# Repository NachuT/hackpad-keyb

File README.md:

# NT KEYB!!!
## Details
  1. Ortholinear custom layout
  2. Minimalist
  3. Cross Wirred PCB
  4. Uses a Pi Pico (or maybe an Orpheus pico 😀)
  5. One piece case but added holes just in case I feel like changing my mind in the future

## BOM
  1. PCB
  2. Case (1 part)
  3. 67 Standard Mx switches
  4. 63 standard 1u keycaps
  5. 1 6u keycap + 6u stabilizer
  6. 3 2u keycaps + 2u stabilizer

## Pictures!

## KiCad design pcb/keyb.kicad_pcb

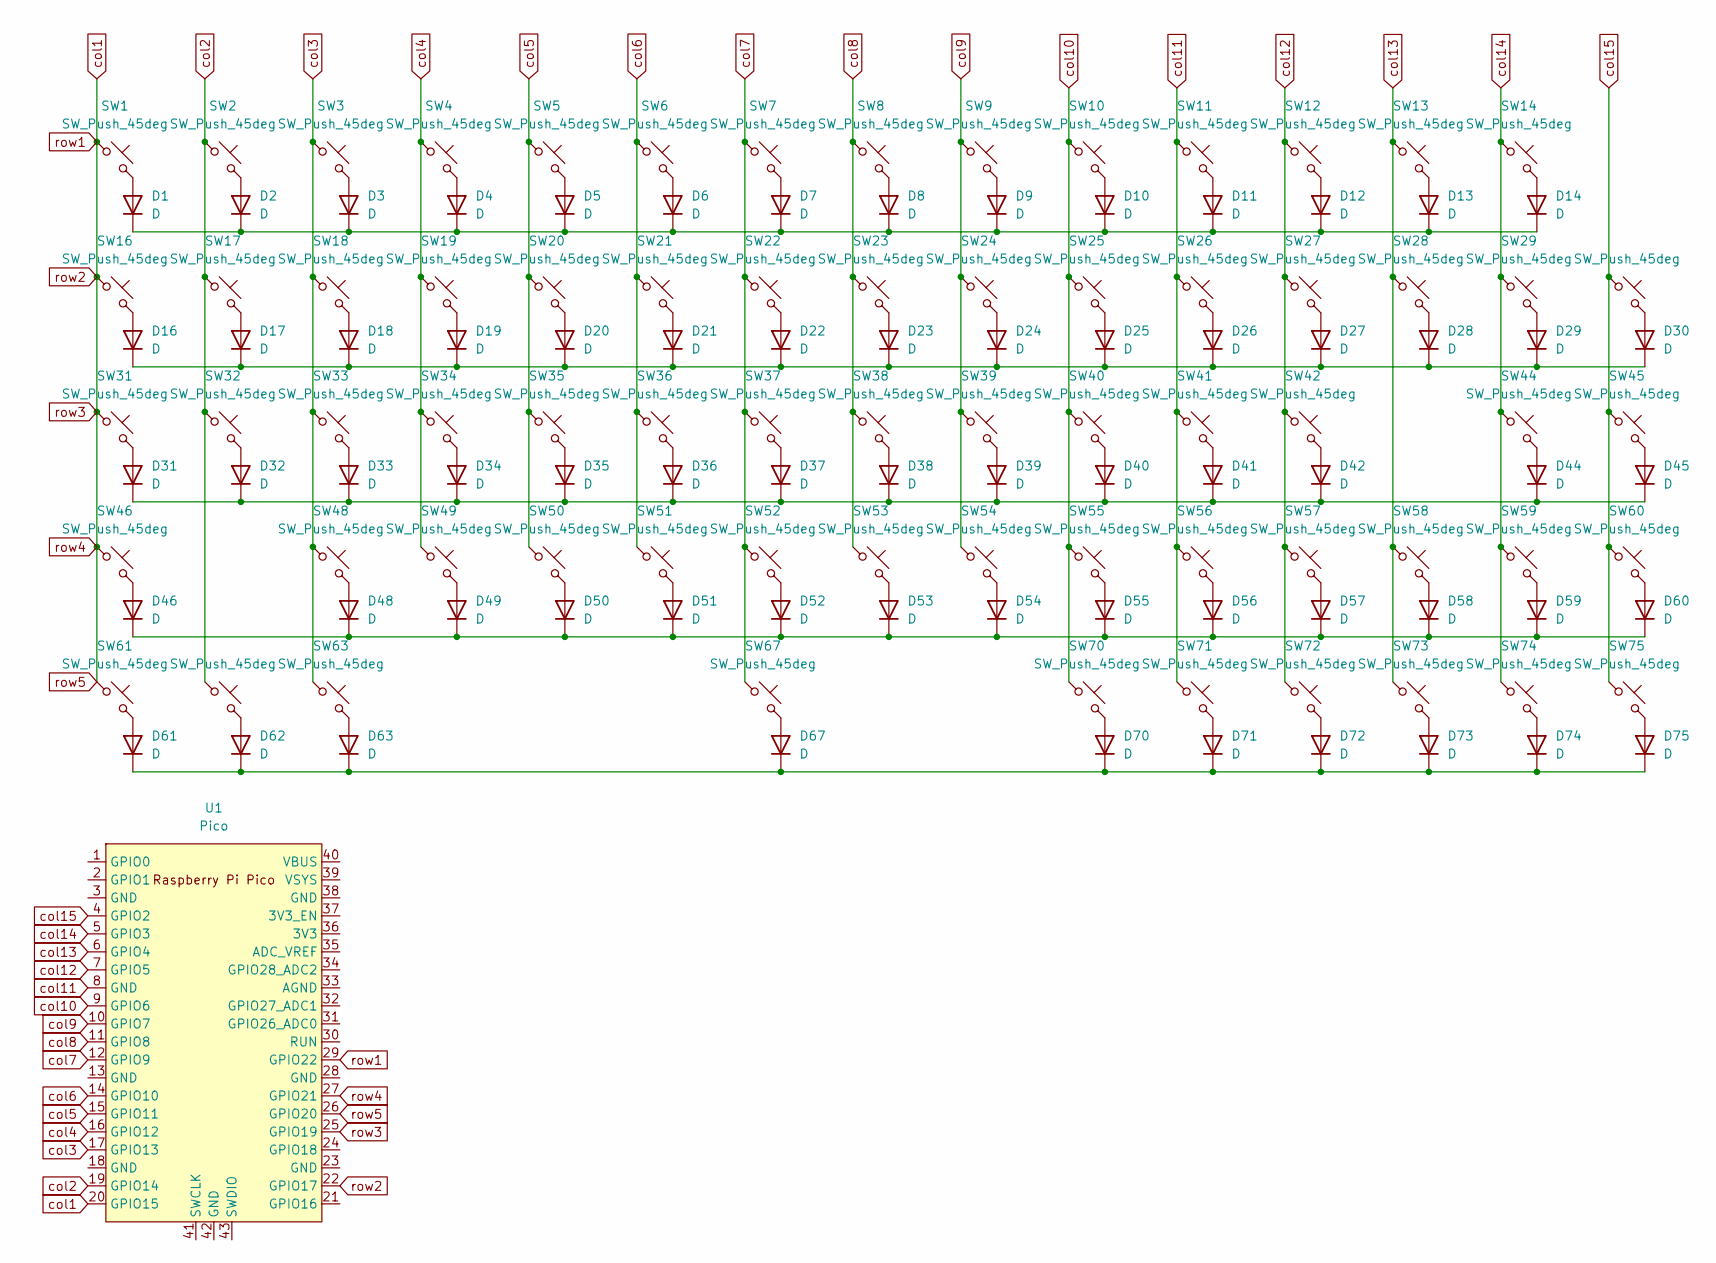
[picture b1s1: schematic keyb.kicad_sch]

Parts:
D1, D2, D3, D4, D5, D6, D7, D8, D9, D10, D11, D12, D13, D14, D16, D17, D18, D19, D20, D21, D22, D23, D24, D25, D26, D27, D28, D29, D30, D31, D32, D33, D34, D35, D36, D37, D38, D39, D40, D41, D42, D44, D45, D46, D48, D49, D50, D51, D52, D53, D54, D55, D56, D57, D58, D59, D60, D61, D62, D63, D67, D70, D71, D72, D73, D74, D75: D; Diode_DO-35
SW1, SW2, SW3, SW4, SW5, SW6, SW7, SW8, SW9, SW10, SW11, SW12, SW13, SW16, SW17, SW18, SW19, SW20, SW21, SW22, SW23, SW24, SW25, SW26, SW27, SW28, SW29, SW30, SW31, SW32, SW33, SW34, SW35, SW36, SW37, SW38, SW39, SW40, SW41, SW42, SW45, SW48, SW49, SW50, SW51, SW52, SW53, SW54, SW55, SW56, SW57, SW58, SW59, SW60, SW61, SW62, SW63, SW70, SW71, SW72, SW73, SW74, SW75: SW_Push_45deg; SW_Cherry_MX_1.00u_PCB
SW14, SW44, SW46: SW_Push_45deg; SW_Cherry_MX_2.00u_PCB
SW67: SW_Push_45deg; MX-6U
U1: Pico; RaspberryPi_Pico_Common_THT

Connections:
unnamed: D1.2 (A), SW1.2
unnamed: D1.1 (K), D2.1 (K), D3.1 (K), D4.1 (K), D5.1 (K), D6.1 (K), D7.1 (K), D8.1 (K), D9.1 (K), D10.1 (K), D11.1 (K), D12.1 (K), D13.1 (K), D14.1 (K)
unnamed: D2.2 (A), SW2.2
unnamed: D3.2 (A), SW3.2
unnamed: D4.2 (A), SW4.2
unnamed: D5.2 (A), SW5.2
unnamed: D6.2 (A), SW6.2
unnamed: D7.2 (A), SW7.2
unnamed: D8.2 (A), SW8.2
unnamed: D9.2 (A), SW9.2
unnamed: D10.2 (A), SW10.2
unnamed: D11.2 (A), SW11.2
unnamed: D12.2 (A), SW12.2
unnamed: D13.2 (A), SW13.2
unnamed: D14.2 (A), SW14.2
unnamed: D16.2 (A), SW16.2
unnamed: D16.1 (K), D17.1 (K), D18.1 (K), D19.1 (K), D20.1 (K), D21.1 (K), D22.1 (K), D23.1 (K), D24.1 (K), D25.1 (K), D26.1 (K), D27.1 (K), D28.1 (K), D29.1 (K), D30.1 (K)
unnamed: D17.2 (A), SW17.2
unnamed: D18.2 (A), SW18.2
unnamed: D19.2 (A), SW19.2
unnamed: D20.2 (A), SW20.2
unnamed: D21.2 (A), SW21.2
unnamed: D22.2 (A), SW22.2
unnamed: D23.2 (A), SW23.2
unnamed: D24.2 (A), SW24.2
unnamed: D25.2 (A), SW25.2
unnamed: D26.2 (A), SW26.2
unnamed: D27.2 (A), SW27.2
unnamed: D28.2 (A), SW28.2
unnamed: D29.2 (A), SW29.2
unnamed: D30.2 (A), SW30.2
unnamed: D31.2 (A), SW31.2
unnamed: D31.1 (K), D32.1 (K), D33.1 (K), D34.1 (K), D35.1 (K), D36.1 (K), D37.1 (K), D38.1 (K), D39.1 (K), D40.1 (K), D41.1 (K), D42.1 (K), D44.1 (K), D45.1 (K)
unnamed: D32.2 (A), SW32.2
unnamed: D33.2 (A), SW33.2
unnamed: D34.2 (A), SW34.2
unnamed: D35.2 (A), SW35.2
unnamed: D36.2 (A), SW36.2
unnamed: D37.2 (A), SW37.2
unnamed: D38.2 (A), SW38.2
unnamed: D39.2 (A), SW39.2
unnamed: D40.2 (A), SW40.2
unnamed: D41.2 (A), SW41.2
unnamed: D42.2 (A), SW42.2
unnamed: D44.2 (A), SW44.2
unnamed: D45.2 (A), SW45.2
unnamed: D46.2 (A), SW46.2
unnamed: D46.1 (K), D48.1 (K), D49.1 (K), D50.1 (K), D51.1 (K), D52.1 (K), D53.1 (K), D54.1 (K), D55.1 (K), D56.1 (K), D57.1 (K), D58.1 (K), D59.1 (K), D60.1 (K)
unnamed: D48.2 (A), SW48.2
unnamed: D49.2 (A), SW49.2
unnamed: D50.2 (A), SW50.2
unnamed: D51.2 (A), SW51.2
unnamed: D52.2 (A), SW52.2
unnamed: D53.2 (A), SW53.2
unnamed: D54.2 (A), SW54.2
unnamed: D55.2 (A), SW55.2
unnamed: D56.2 (A), SW56.2
unnamed: D57.2 (A), SW57.2
unnamed: D58.2 (A), SW58.2
unnamed: D59.2 (A), SW59.2
unnamed: D60.2 (A), SW60.2
unnamed: D61.2 (A), SW61.2
unnamed: D61.1 (K), D62.1 (K), D63.1 (K), D67.1 (K), D70.1 (K), D71.1 (K), D72.1 (K), D73.1 (K), D74.1 (K), D75.1 (K)
unnamed: D62.2 (A), SW62.2
unnamed: D63.2 (A), SW63.2
unnamed: D67.2 (A), SW67.2
unnamed: D70.2 (A), SW70.2
unnamed: D71.2 (A), SW71.2
unnamed: D72.2 (A), SW72.2
unnamed: D73.2 (A), SW73.2
unnamed: D74.2 (A), SW74.2
unnamed: D75.2 (A), SW75.2
col1: SW1.1, SW16.1, SW31.1, SW46.1, SW61.1, U1.20 (GPIO15), U1.22 (GPIO17), U1.25 (GPIO19), U1.26 (GPIO20), U1.27 (GPIO21), U1.29 (GPIO22)
col2: SW2.1, SW17.1, SW32.1, SW62.1, U1.19 (GPIO14)
col3: SW3.1, SW18.1, SW33.1, SW48.1, SW63.1, U1.17 (GPIO13)
col4: SW4.1, SW19.1, SW34.1, SW49.1, U1.16 (GPIO12)
col5: SW5.1, SW20.1, SW35.1, SW50.1, U1.15 (GPIO11)
col6: SW6.1, SW21.1, SW36.1, SW51.1, U1.14 (GPIO10)
col7: SW7.1, SW22.1, SW37.1, SW52.1, SW67.1, U1.12 (GPIO9)
col8: SW8.1, SW23.1, SW38.1, SW53.1, U1.11 (GPIO8)
col9: SW9.1, SW24.1, SW39.1, SW54.1, U1.10 (GPIO7)
col10: SW10.1, SW25.1, SW40.1, SW55.1, SW70.1, U1.9 (GPIO6)
col11: SW11.1, SW26.1, SW41.1, SW56.1, SW71.1, U1.8 (GND)
col12: SW12.1, SW27.1, SW42.1, SW57.1, SW72.1, U1.7 (GPIO5)
col13: SW13.1, SW28.1, SW58.1, SW73.1, U1.6 (GPIO4)
col14: SW14.1, SW29.1, SW44.1, SW59.1, SW74.1, U1.5 (GPIO3)
col15: SW30.1, SW45.1, SW60.1, SW75.1, U1.4 (GPIO2)

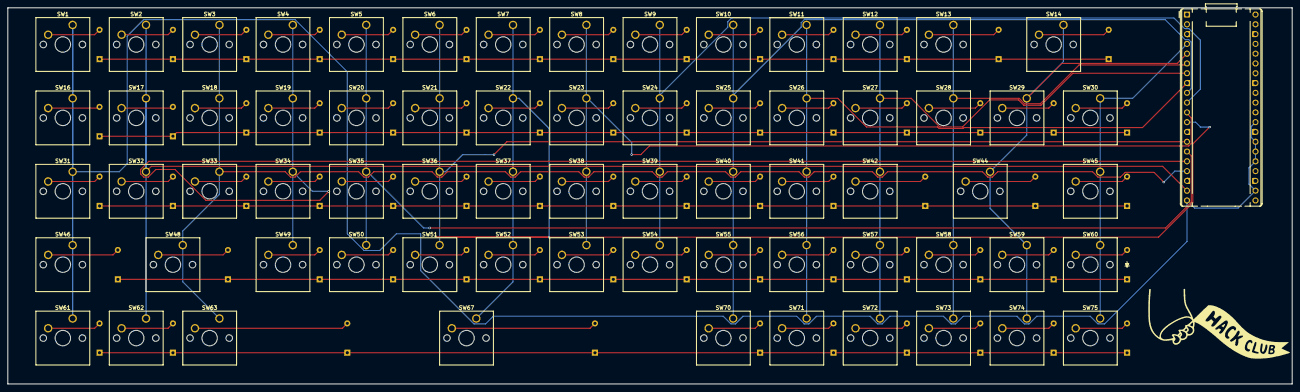
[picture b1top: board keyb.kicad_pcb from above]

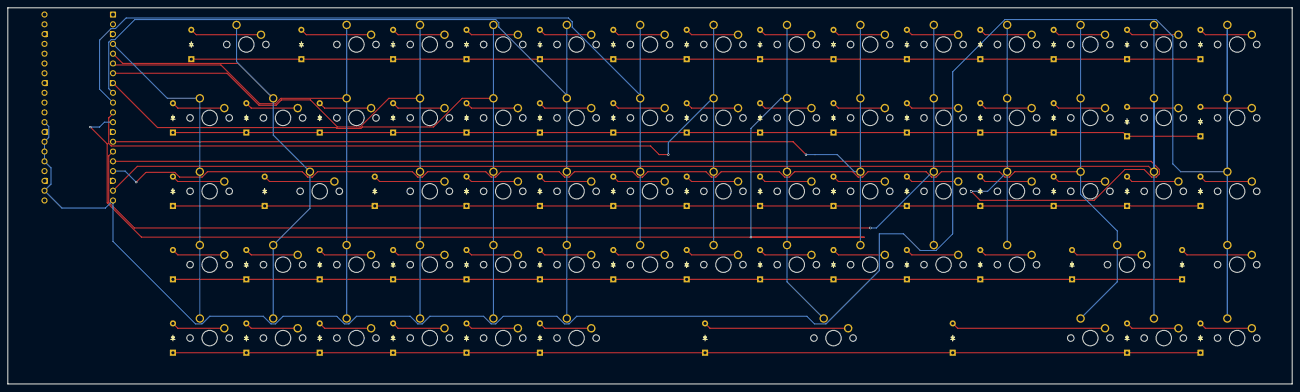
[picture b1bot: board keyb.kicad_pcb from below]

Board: 2 copper layers, 333.4 x 97.6 mm, 135 parts (66 on the bottom side), 87 nets.

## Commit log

2025-03-09 Rename fp-lib-table to pcb/fp-lib-table
2025-03-09 Rename keyb.kicad_pcb to pcb/keyb.kicad_pcb
2025-03-09 Rename keyb.kicad_prl to pcb/keyb.kicad_prl
2025-03-09 Rename keyb.kicad_pro to pcb/keyb.kicad_pro
2025-03-09 Rename keyb.kicad_sch to pcb/keyb.kicad_sch
2025-03-09 Rename keyb.kicad_sch-bak to pcb/keyb.kicad_sch-bak
2025-03-09 Rename keybv1.step to cad/keybv1.step
